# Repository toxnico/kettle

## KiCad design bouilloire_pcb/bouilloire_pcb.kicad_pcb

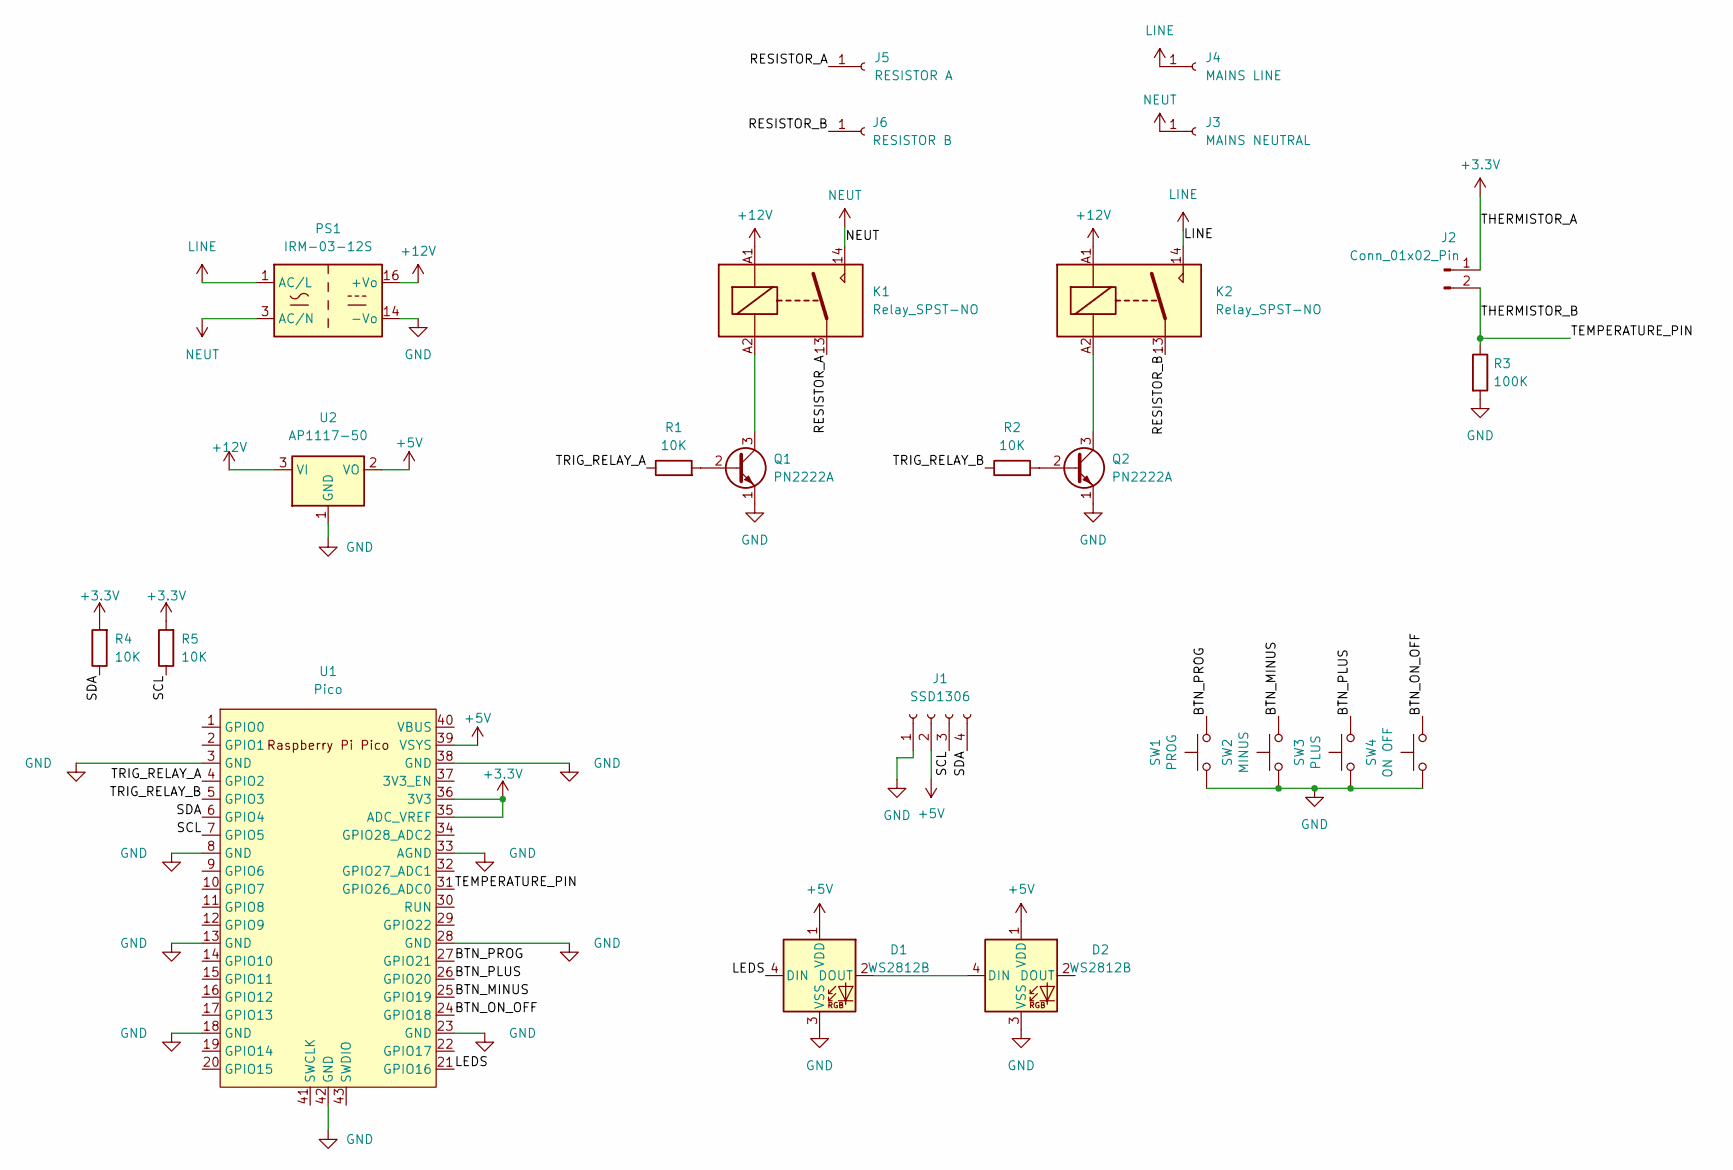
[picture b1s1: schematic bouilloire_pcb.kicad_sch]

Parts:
D1, D2: WS2812B; LED_WS2812B_PLCC4_5.0x5.0mm_P3.2mm
J1: SSD1306; PinSocket_1x04_P2.54mm_Vertical
J2: Conn_01x02_Pin; JST_XH_B2B-XH-A_1x02_P2.50mm_Vertical
J3: MAINS NEUTRAL; mains connector
J4: MAINS LINE; mains connector
J5: RESISTOR A; PinSocket_1x01_P2.54mm_Vertical
J6: RESISTOR B; PinSocket_1x01_P2.54mm_Vertical
K1, K2: Relay_SPST-NO; relay_RZHH 1 form A NO
PS1: IRM-03-12S; Converter_ACDC_MeanWell_IRM-03-xx_SMD
Q1, Q2: PN2222A; SOT-23 - 2N2222 BEC
R1, R2, R4, R5: 10K; R_0805_2012Metric_Pad1.20x1.40mm_HandSolder
R3: 100K; R_0805_2012Metric_Pad1.20x1.40mm_HandSolder
SW1: PROG; SW_PUSH_6mm_H4.3mm
SW2: MINUS; SW_PUSH_6mm_H4.3mm
SW3: PLUS; SW_PUSH_6mm_H4.3mm
SW4: ON OFF; SW_PUSH_6mm_H4.3mm
U1: Pico; RPi_Pico_SMD_TH
U2: AP1117-50; SOT-223-3_TabPin2

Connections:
+3.3V: J2.1, R4.2, R5.2, U1.35 (ADC_VREF), U1.36 (3V3)
+5V: D1.1 (VDD), D2.1 (VDD), J1.2, U1.39 (VSYS), U2.2 (VO)
+12V: K1.A1, K2.A1, PS1.16 (+Vo), U2.3 (VI)
/BTN_MINUS: SW2.2, U1.25 (GPIO19)
/BTN_ON_OFF: SW4.2, U1.24 (GPIO18)
/BTN_PLUS: SW3.2, U1.26 (GPIO20)
/BTN_PROG: SW1.2, U1.27 (GPIO21)
/LEDS: D1.4 (DIN), U1.21 (GPIO16)
/RESISTOR_A: J5.1, K1.13
/RESISTOR_B: J6.1, K2.13
/SCL: J1.3, R5.1, U1.7 (GPIO5)
/SDA: J1.4, R4.1, U1.6 (GPIO4)
/TEMPERATURE_PIN: J2.2, R3.1, U1.31 (GPIO26_ADC0)
/TRIG_RELAY_A: R1.1, U1.4 (GPIO2)
/TRIG_RELAY_B: R2.1, U1.5 (GPIO3)
GND: D1.3 (VSS), D2.3 (VSS), J1.1, PS1.14 (-Vo), Q1.1 (E), Q2.1 (E), R3.2, SW1.1, SW2.1, SW3.1, SW4.1, U1.3 (GND), U1.8 (GND), U1.13 (GND), U1.18 (GND), U1.23 (GND), U1.28 (GND), U1.33 (AGND), U1.38 (GND), U1.42 (GND), U2.1 (GND)
LINE: J4.1, K2.14, PS1.1 (AC/L)
NEUT: J3.1, K1.14, PS1.3 (AC/N)
unnamed: D1.2 (DOUT), D2.4 (DIN)
unnamed: Q1.2 (B), R1.2
unnamed: K1.A2, Q1.3 (C)
unnamed: Q2.2 (B), R2.2
unnamed: K2.A2, Q2.3 (C)

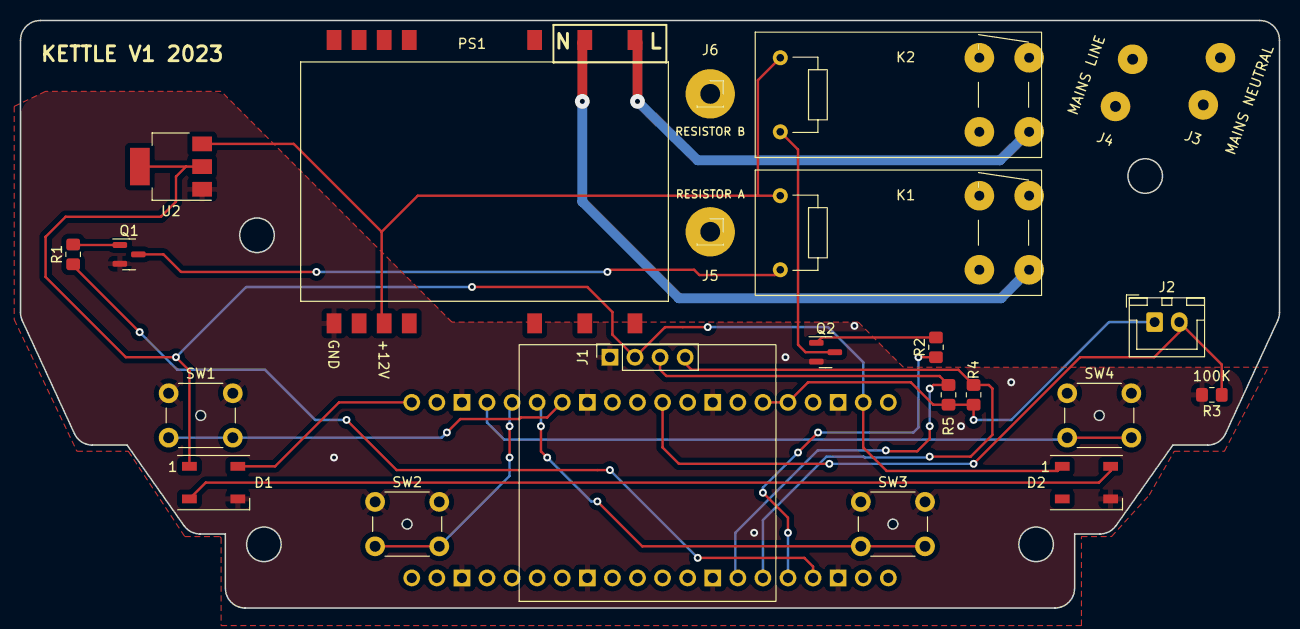
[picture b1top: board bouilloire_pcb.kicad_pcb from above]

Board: 2 copper layers, 127.5 x 59.5 mm, 24 parts (1 on the bottom side), 23 nets.

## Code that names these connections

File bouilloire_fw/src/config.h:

#ifndef CONFIG_H
#define CONFIG_H

#define PIN_RELAY_A 2
#define PIN_RELAY_B 3
#define PIN_SDA 4
#define PIN_SCL 5
#define PIN_TEMPERATURE 26

#define PIN_BTN_ON_OFF 18
#define PIN_BTN_PLUS 19
#define PIN_BTN_MINUS 20
#define PIN_BTN_PROG 21

#define PIN_LEDS 16

#define ABSOLUTE_MIN_TEMPERATURE 20
#define ABSOLUTE_MAX_TEMPERATURE 90

//coefficients of the equation temp = a * x + b
#define TEMP_CONVERSION_A 0.0341456166419019
#define TEMP_CONVERSION_B (-39.8855869242199 + 5)

//Value in degrees. If the measured value is lower than this, the relays are forced to off
#define MINIMUM_VALID_TEMPERATURE 0

#define TEMPERATURE_HYSTERESIS 5

#define READ_TEMP_INTERVAL_US 1000000

// 5 minutes without touching anything switches off the system
#define AUTO_OFF_TIMEOUT_US (5*60*1000000) 
//#define AUTO_OFF_TIMEOUT_US 10000000


#endif //CONFIG_H

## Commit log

2023-12-23 update + and - and max temperature
